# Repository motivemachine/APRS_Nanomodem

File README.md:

# APRS NanoModem

My PCB design for an APRS TNC, based on Mark Qvist's excellent MicroModem design. Can be used as a standalone TNC or controlled by several serial protocols. Castellated and through-hole design allows space-saving mounting on larger boards SMD style, or easy use with perfboard, breadboard, or jumper wires.

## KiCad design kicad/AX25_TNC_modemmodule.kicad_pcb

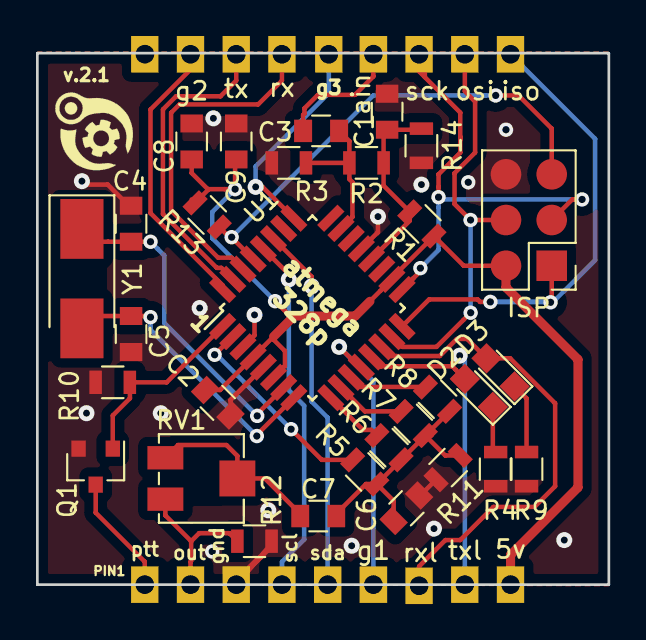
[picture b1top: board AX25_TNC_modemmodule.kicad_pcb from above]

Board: 2 copper layers, 31.8 x 29.5 mm, 47 parts (0 on the bottom side), 31 nets.

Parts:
5v: Conn_01x01_Female; Castleated_Pad_1
C1, C2: .1uf; C_0805
C3: 1uf; C_0805
C4, C5: 18pf; C_0805
C6, C8: 100nf; C_0805
C7: 4.7uf; C_0805
C9: 10uf; C_0805
D2: tx; LED_0805
D3: rx; LED_0805
ISP: AVR-ISP-6; Pin_Header_Straight_2x03_Pitch2.54mm
J14: gen2; Castleated_Pad_1
Q1: BSS138; SOT-23
R1, R2, R3: 100k; R_0805
R4, R9: 4k7; R_0805
R5: 8k2; R_0805
R6: 3k9; R_0805
R7: 2k2; R_0805
R8, R12: 1k; R_0805
R10, R13: 10k; R_0805
R11: 270; R_0805
R14: 200k; R_0805
RV1: R_POT_TRIM_US; Potentiometer_Trimmer_Bourns_3224J
U1: ATmega328P-AU; TQFP-32_7x7mm_Pitch0.8mm
Y1: 16Mhz; Crystal_SMD_Abracon_ABM3-2pin_5.0x3.2mm_HandSoldering
ain: Conn_01x01_Female; Castleated_Pad_1
g1: gen1; Castleated_Pad_1
g2: Conn_01x01_Female; Castleated_Pad_1
gnd: Conn_01x01_Female; Castleated_Pad_1
iso: Conn_01x01_Female; Castleated_Pad_1
osi: Conn_01x01_Female; Castleated_Pad_1
out: Conn_01x01_Female; Castleated_Pad_1
ptt: Conn_01x01_Female; Castleated_Pad_1
rx: gen3; Castleated_Pad_1
rxl: rxled; Castleated_Pad_1
sck: Conn_01x01_Female; Castleated_Pad_1
scl: Conn_01x01_Female; Castleated_Pad_1
sda: Conn_01x01_Female; Castleated_Pad_1
tx: Conn_01x01_Female; Castleated_Pad_1
txl: txled; Castleated_Pad_1

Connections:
+5V: 5v.9, C2.2, C8.1, C9.1, ISP.2, R1.1, R13.1, U1.4, U1.6, U1.18
/audio_bias: C1.2, R1.2, R2.1, R14.1, U1.20
/audio_in: C3.1, ain.1
/audio_out: R12.1, RV1.1, out.2
/gen1: U1.12, g1.6
/gen2: J14.1, U1.32
/gen3: U1.25, rx.1
/miso: ISP.1, U1.16, iso.10
/mosi: ISP.4, U1.15, osi.11
/ptt: Q1.3, ptt.1
/reset: ISP.5, R13.2, U1.29
/rxled: D3.2, U1.14, rxl.7
/sck: ISP.3, U1.17, sck.1
/scl: U1.28, scl.4
/sda: U1.27, sda.5
/tnc_rx: U1.30, tx.1
/tnc_tx: U1.31, g2.1
/txled: D2.2, U1.13, txl.8
GND: C1.1, C2.1, C4.1, C5.1, C6.2, C8.2, C9.2, ISP.6, Q1.2, R3.2, R4.1, R9.1, R10.1, R11.1, R12.2, R14.2, U1.3, U1.5, U1.21, gnd.3
unnamed: C3.2, R2.2, R3.1, U1.23
unnamed: C4.2, U1.7, Y1.1
unnamed: C5.2, U1.8, Y1.2
unnamed: C6.1, C7.2, R5.1, R6.1, R7.1, R8.1, R11.2
unnamed: C7.1, RV1.2, RV1.3
unnamed: D2.1, R4.2
unnamed: D3.1, R9.2
unnamed: Q1.1, R10.2, U1.1
unnamed: R5.2, U1.2
unnamed: R6.2, U1.9
unnamed: R7.2, U1.10
unnamed: R8.2, U1.11

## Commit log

2019-05-25 added gerbers and .sch files
2019-05-27 upload pictures
2019-05-27 Add LICENSE
